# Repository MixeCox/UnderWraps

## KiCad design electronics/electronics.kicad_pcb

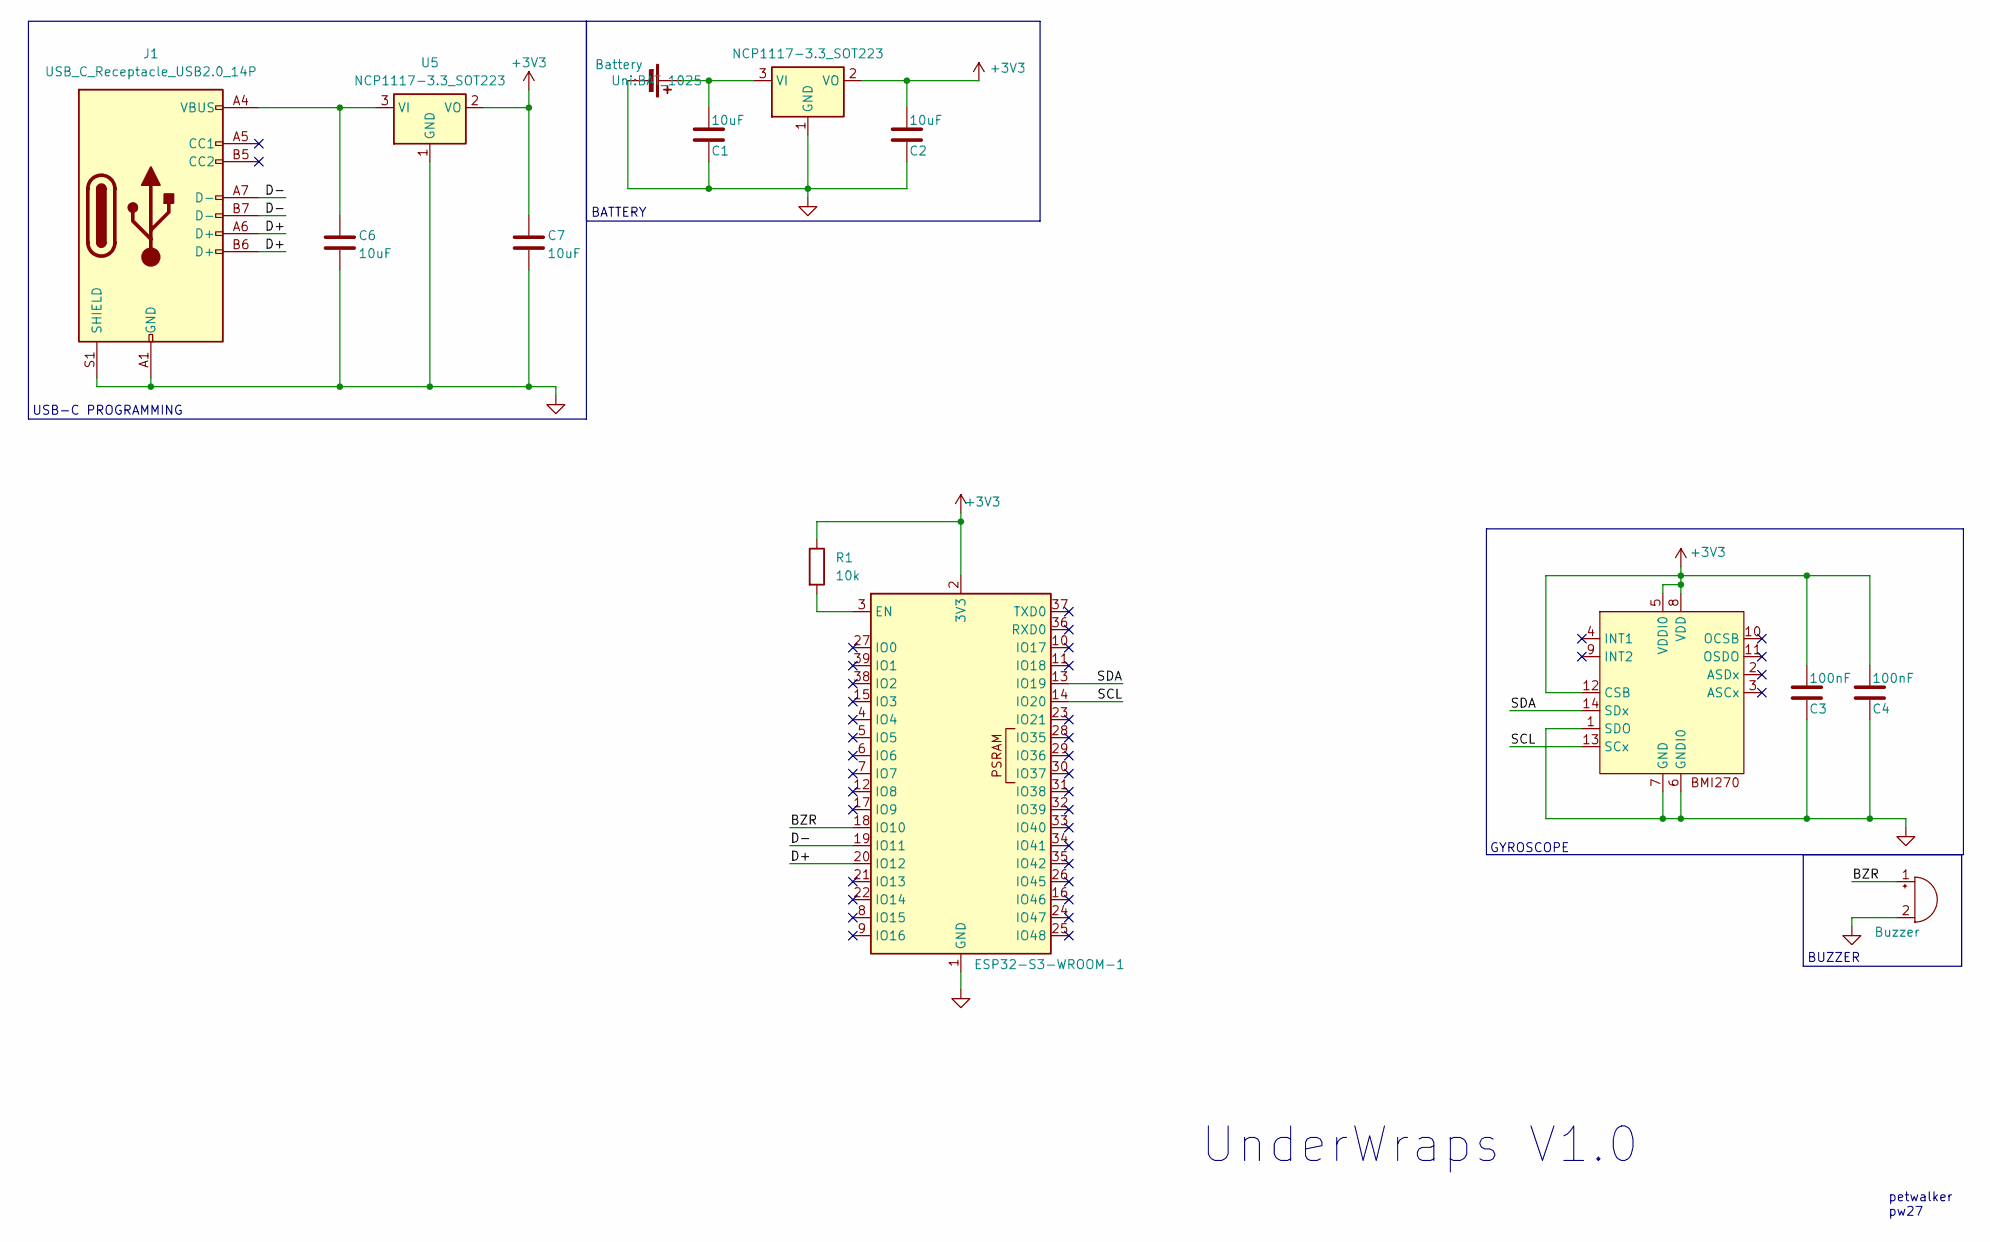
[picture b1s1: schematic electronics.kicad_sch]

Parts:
BT1: Battery; BAT_1025
BZ1: Buzzer; SPKR_PKMCS0909E4000-R1
C1, C2, C6, C7: 10uF; C_0805_2012Metric
C3, C4: 100nF; C_0603_1608Metric
J1: USB_C_Receptacle_USB2.0_14P; USB_C_Receptacle_GCT_USB4110
R1: 10k; R_0402_1005Metric
U1: ESP32-S3-WROOM-1
U2: Bosch_LGA-14_3x2.5mm_P0.5mm
U3, U5: NCP1117-3.3_SOT223; SOT-223-3_TabPin2

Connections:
+3V3: C2.1, C3.1, C4.1, C7.1, R1.1, U1.2 (3V3), U2.5 (VDDI0), U2.8 (VDD), U2.12 (CSB), U3.2 (VO), U5.2 (VO)
/BZR: BZ1.1 (+), U1.18 (IO10)
/D+: J1.A6 (D+), J1.B6 (D+), U1.20 (IO12)
/D-: J1.A7 (D-), J1.B7 (D-), U1.19 (IO11)
/SCL: U1.14 (IO20), U2.13 (SCx)
/SDA: U1.13 (IO19), U2.14 (SDx)
GND: BT1.2 (-), BZ1.2 (-), C1.2, C2.2, C3.2, C4.2, C6.2, C7.2, J1.A1 (GND), J1.A12 (GND), J1.B1 (GND), J1.B12 (GND), J1.S1 (SHIELD), U1.1 (GND), U1.40 (GND), U1.41 (GND), U2.1 (SDO), U2.6 (GNDI0), U2.7 (GND), U3.1 (GND), U5.1 (GND)
unnamed: BT1.1 (+), C1.1, U3.3 (VI)
unnamed: R1.2, U1.3 (EN)
unnamed: C6.1, J1.A4 (VBUS), J1.A9 (VBUS), J1.B4 (VBUS), J1.B9 (VBUS), U5.3 (VI)

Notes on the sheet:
USB-C PROGRAMMING
petwalker pw27
BATTERY
UnderWraps V1.0
GYROSCOPE
BUZZER

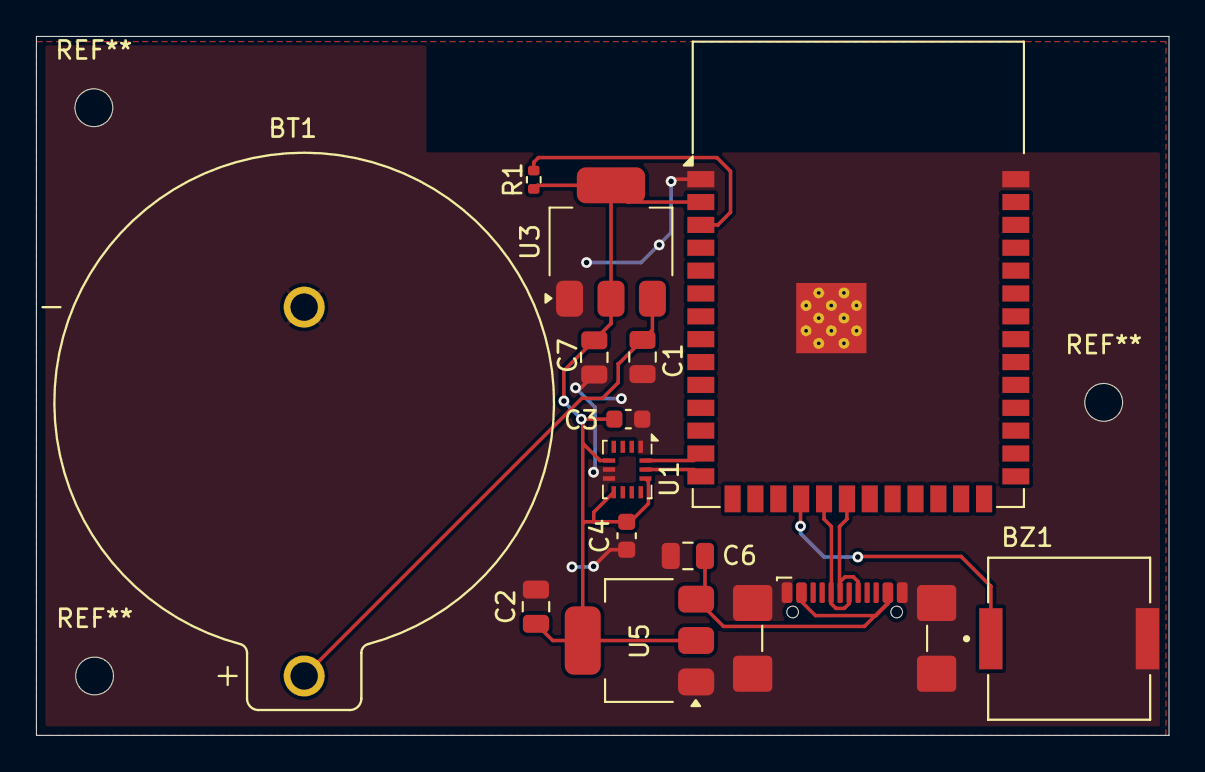
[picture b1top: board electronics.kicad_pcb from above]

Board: 2 copper layers, 62.9 x 38.8 mm, 14 parts (0 on the bottom side), 10 nets.

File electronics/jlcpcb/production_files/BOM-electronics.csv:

Comment,Designator,Footprint,LCSC,Quantity
10k,R1,R_0402_1005Metric,C119202,1
Battery,BT1,BAT_1025,C238061,1
USB_C_Receptacle_USB2.0_14P,J1,USB_C_Receptacle_GCT_USB4110,C2761226,1
NCP1117-3.3_SOT223,"U3,U5",SOT-223-3_TabPin2,C277892,2
~,U2,Bosch_LGA-14_3x2.5mm_P0.5mm,C2836813,1
ESP32-S3-WROOM-1,U1,ESP32-S3-WROOM-1,C2913197,1
100nF,"C3,C4",C_0603_1608Metric,C48579283,2
10uF,"C1,C2,C6,C7",C_0805_2012Metric,C48579582,4
Buzzer,BZ1,SPKR_PKMCS0909E4000-R1,C910763,1

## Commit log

2025-07-19 REACT APP
2025-07-20 Schematic V1
2025-07-21 PCB w/ Gerbers
2025-07-30 PCB but better
2025-07-31 BOM + Gerbers
2025-08-03 BOM + Gerbers: Final Iteration (Hopefully)
